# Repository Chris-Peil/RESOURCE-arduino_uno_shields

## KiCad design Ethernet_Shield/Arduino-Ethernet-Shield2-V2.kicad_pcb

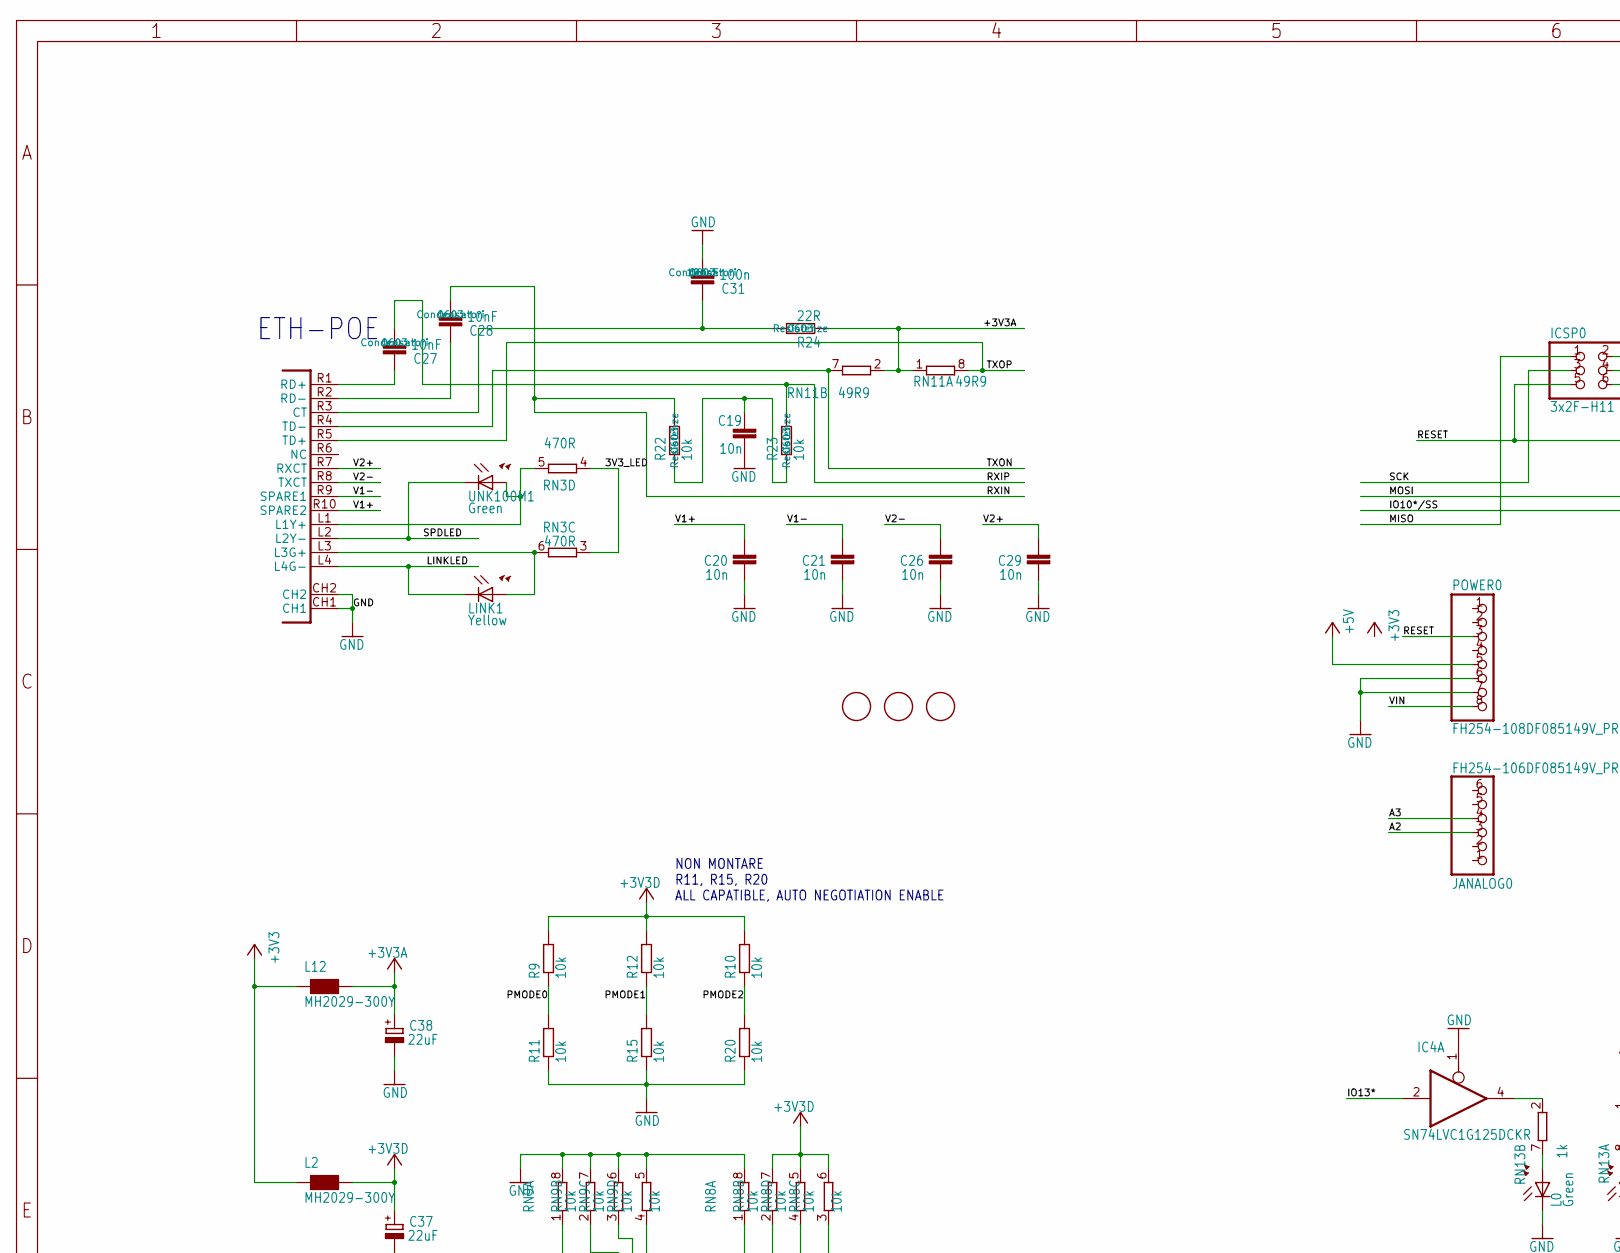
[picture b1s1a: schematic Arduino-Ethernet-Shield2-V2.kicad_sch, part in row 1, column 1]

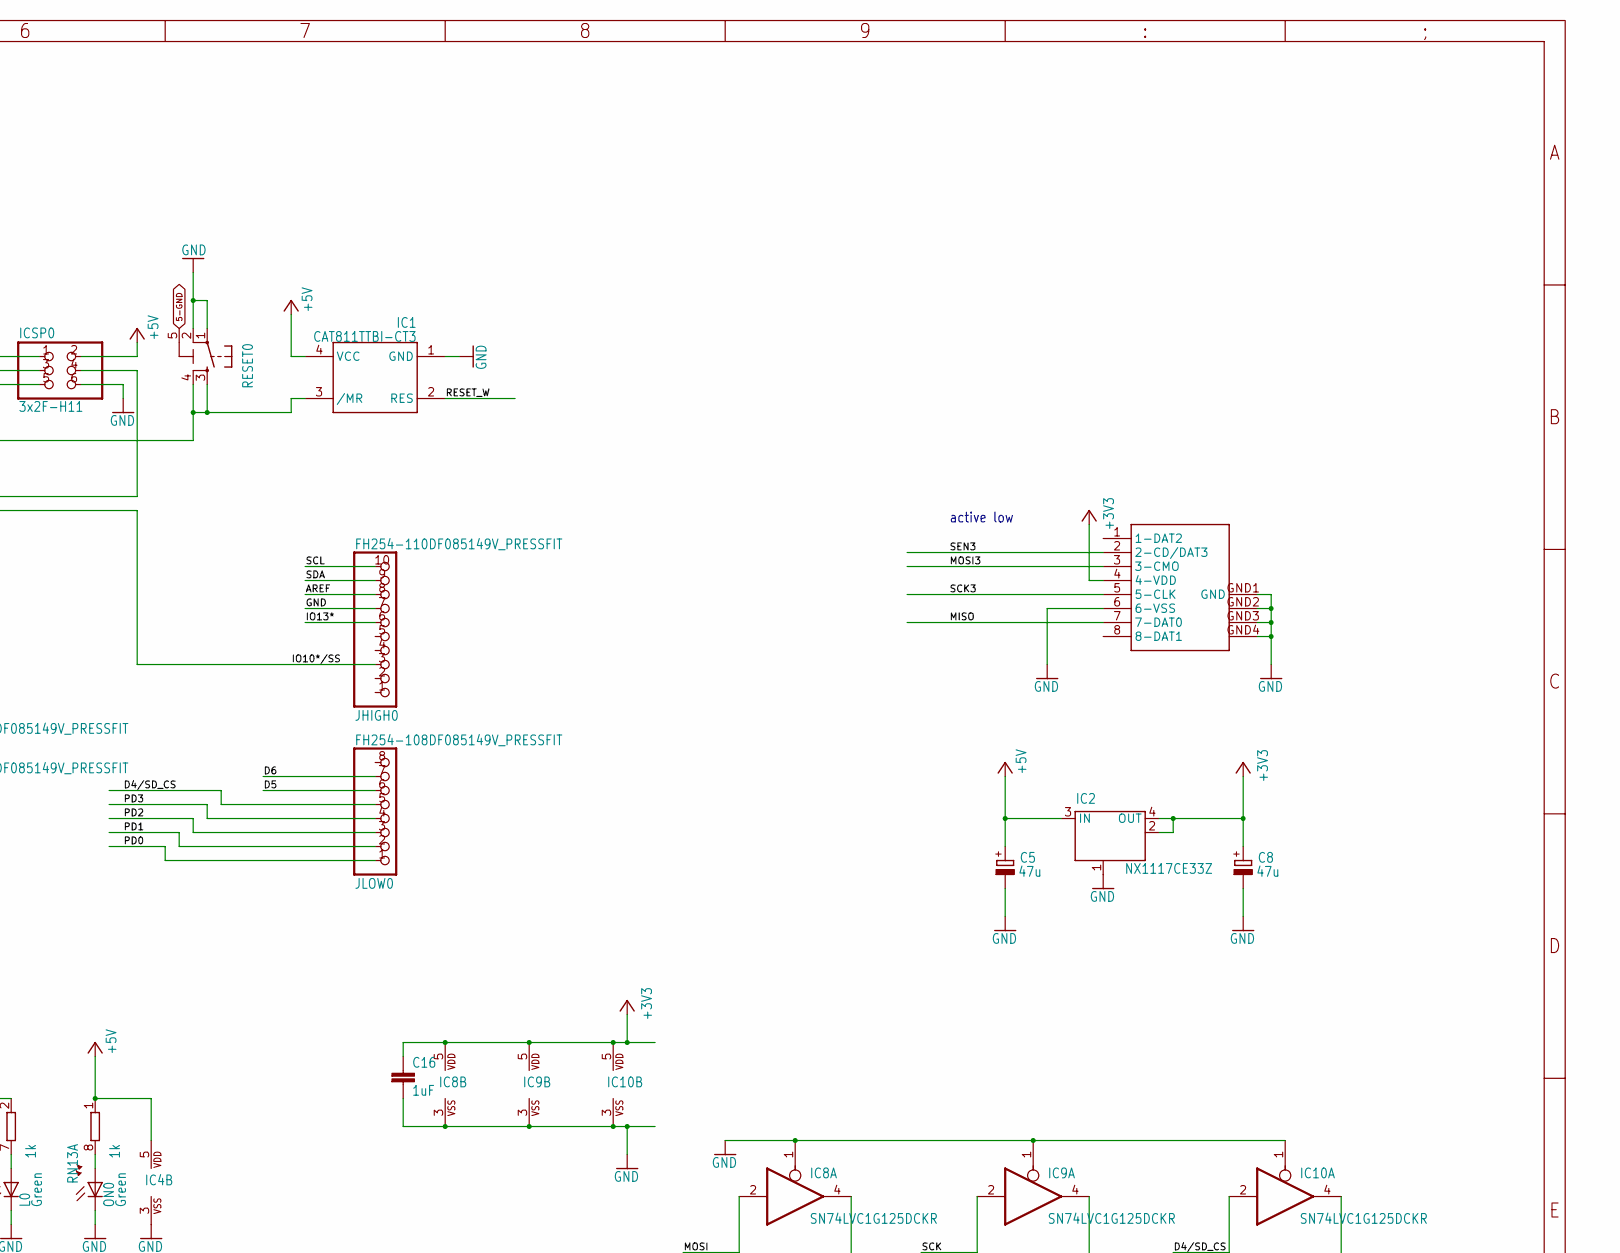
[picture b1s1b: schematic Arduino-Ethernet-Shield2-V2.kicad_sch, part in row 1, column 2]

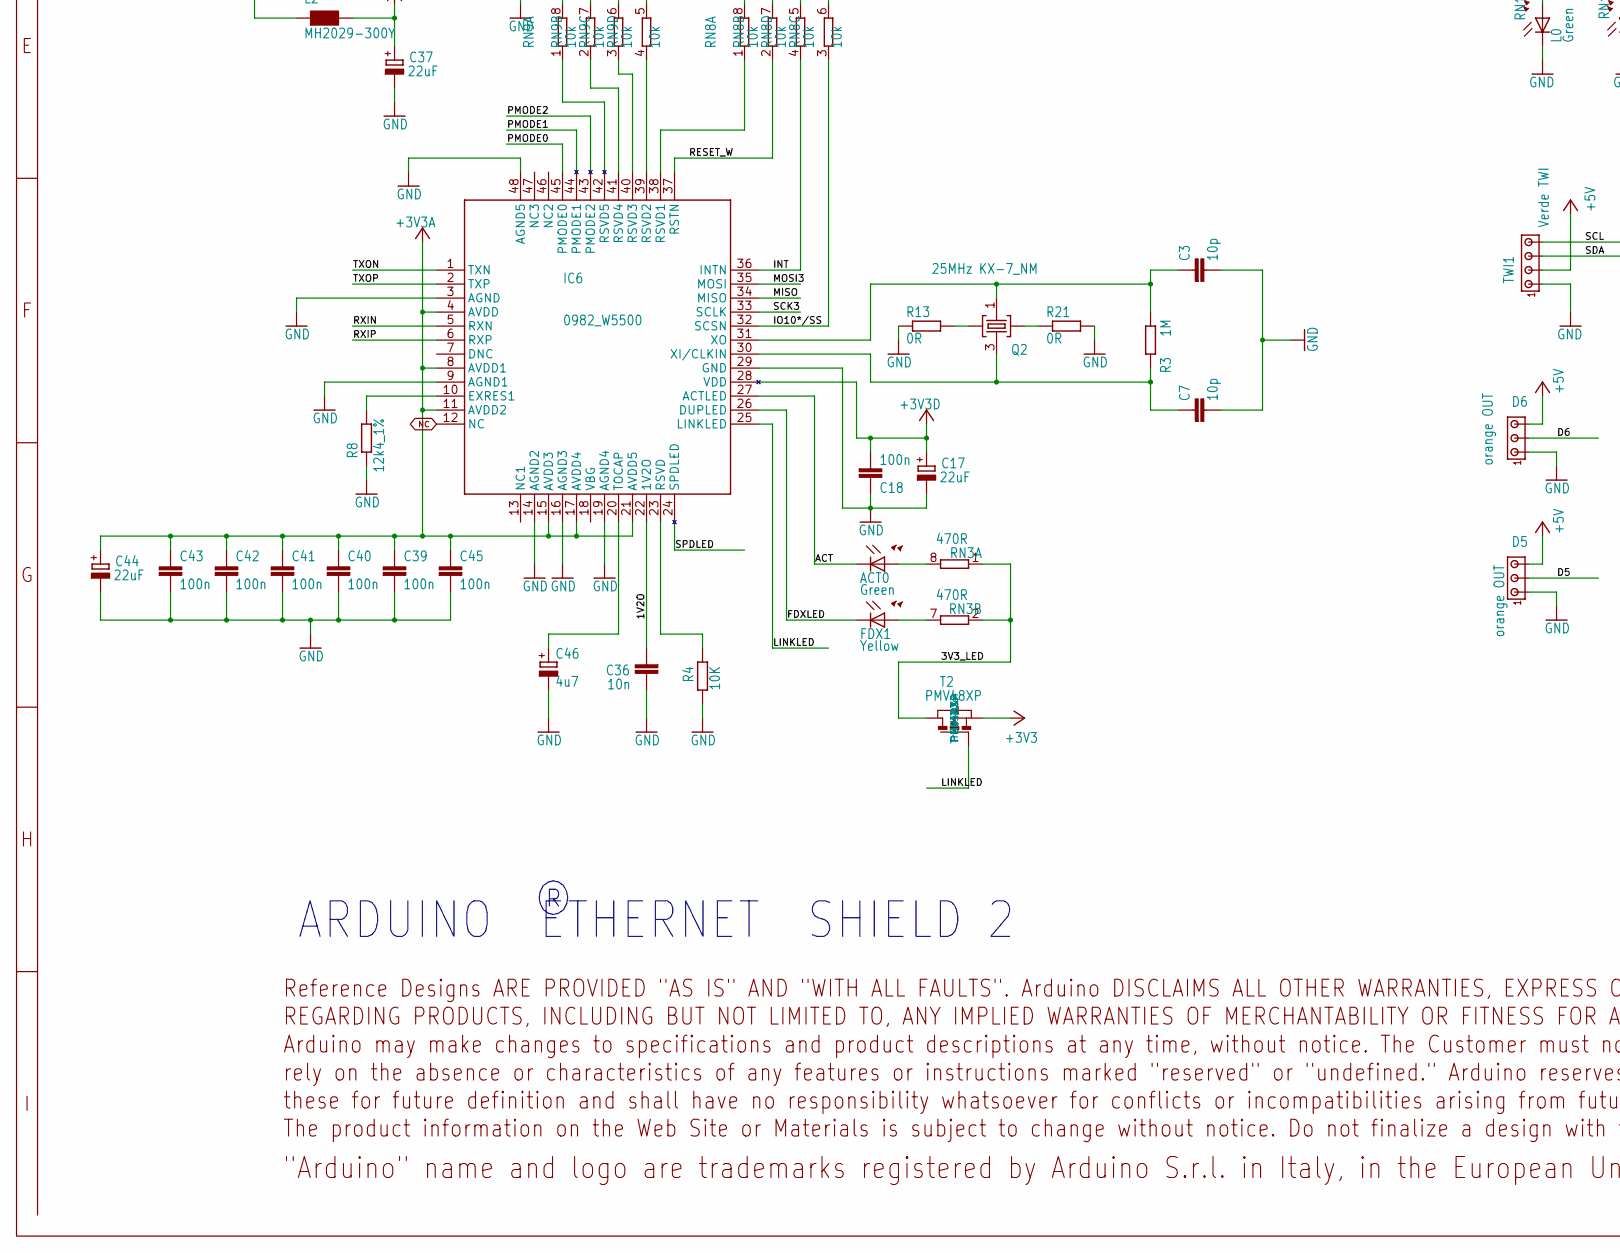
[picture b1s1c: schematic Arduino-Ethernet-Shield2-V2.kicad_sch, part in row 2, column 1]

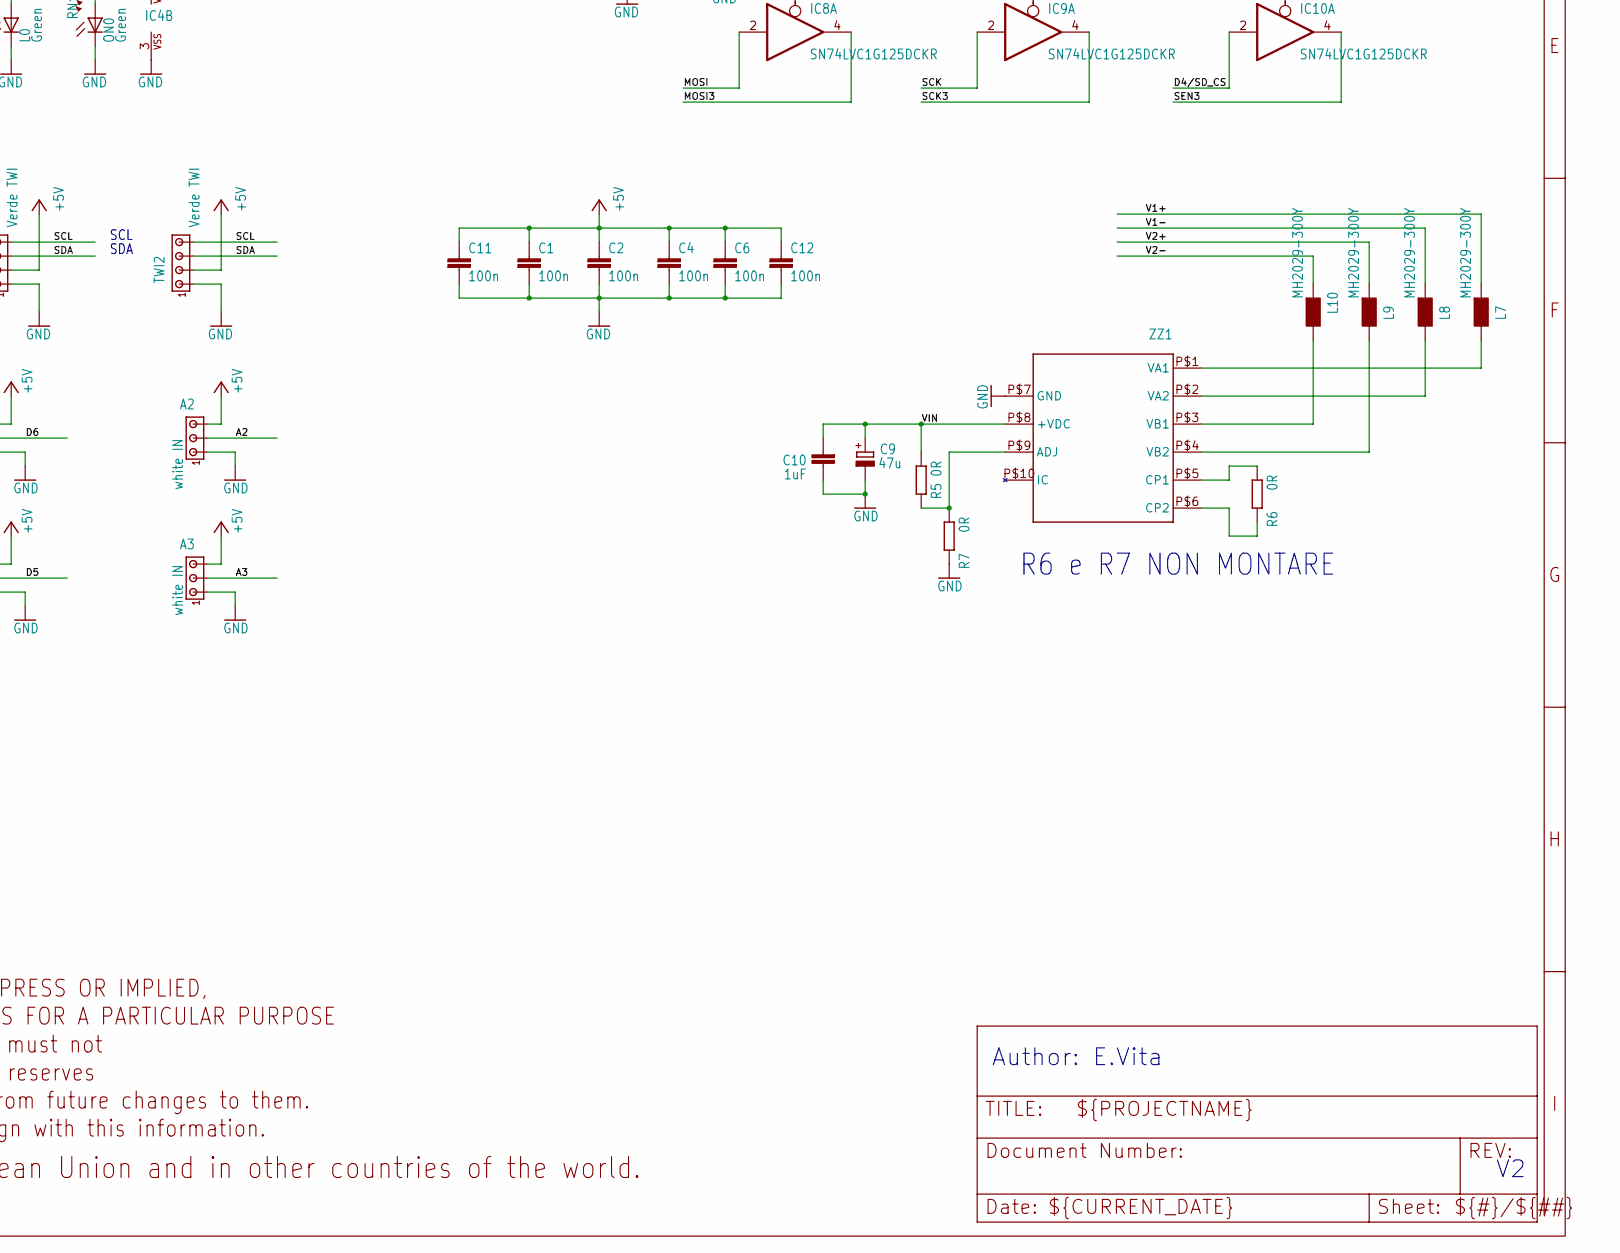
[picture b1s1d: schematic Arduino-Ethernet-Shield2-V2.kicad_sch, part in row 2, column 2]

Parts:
A2, A3: white IN; 10X03MTA
ACT0: Green; CHIPLED_0805
C1, C2, C4, C6, C11, C12, C18, C31, C39, C40, C41, C42, C43, C45: 100n; C0603-ROUND
C3, C7: 10p; C0603-ROUND
C5, C8, C9: 47u; PANASONIC_D
C10, C16: 1uF; C0603-ROUND
C17, C37, C38, C44: 22uF; SMC_B
C19, C20, C21, C26, C29, C36: 10n; C0603-ROUND
C27, C28: 10nF; C0603-ROUND
C46: 4u7; SMC_A
D5, D6: orange OUT; 10X03MTA
FDX1: Yellow; CHIPLED_0805
FID2, FID3, FID4: FIDUCIALMOUNT; FIDUCIA-MOUNT
IC1: CAT811TTBI-CT3; SOT143
IC2: NX1117CE33Z; SOT223
IC4, IC8, IC9, IC10: SN74LVC1G125DCKR; SC70-5
IC6: 0982_W5500; TQFP48-7X7
ICSP0: 3x2F-H11; 2X03
JANALOG0: FH254-106DF085149V_PRESSFIT; 1X06-TH-PRESSFIT
JHIGH0: FH254-110DF085149V_PRESSFIT; 1X10-TH-PRESSFIT
JLOW0: FH254-108DF085149V_PRESSFIT; 1X08-TH-PRESSFIT
L0: Green; CHIPLED_0805
L2, L7, L8, L9, L10, L12: MH2029-300Y; 0805
LINK1: Yellow; CHIPLED_0805
ON0: Green; CHIPLED_0805
POWER0: FH254-108DF085149V_PRESSFIT; 1X08-TH-PRESSFIT
Q2: 25MHz KX-7_NM; CRYSTAL3.2X2.5
R3: 1M; R0603-ROUND
R4: 10K; R0603-ROUND
R5, R6, R7: 0R; R0603-ROUND
R8: 12k4_1%; R0603-ROUND
R9, R10, R11, R12, R15, R20, R22, R23: 10k; R0603-ROUND
R13, R21: 0R; R0402
R24: 22R; R0603-ROUND
RESET0: 0946_TS42031-160W-TR-7260; TS42
RN3: 470R; CAY16
RN8, RN9: 10k; CAY16
RN11: 49R9; CAY16
RN13: 1k; CAY16
T2: PMV48XP; SOT-23; PART_NUMBER PMV48XP
TWI1, TWI2: Verde TWI; 10X04MTA
U$1: DISCLAIMER
UC1: RB1-125BHQ1A; POE-RJ45
UNK100M1: Green; CHIPLED_0805
X1: 0046_15TW-882; SDCARD-15TW-8821
ZZ1: 0343_AG9612-2BR; AG9000

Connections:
1V2O: C36.2, IC6.22 (1V2O)
3V3_LED: RN3.1, RN3.2 (1), RN3.3 (1), RN3.4 (1), T2.1 (D)
5-GND: RESET0.5 (5-GND)
+3V3: C8.+, C16.1, IC2.2 (OUT@1), IC2.4 (OUT), IC8.5 (VDD), IC9.5 (VDD), IC10.5 (VDD), L2.1, L12.1, T2.2 (S), X1.4 (4-VDD)
+3V3A: C38.+, C39.1, C40.1, C41.1, C42.1, C43.1, C44.+, C45.1, IC6.4 (AVDD), IC6.8 (AVDD1), IC6.11 (AVDD2), IC6.15 (AVDD3), IC6.17 (AVDD4), IC6.21 (AVDD5), L12.2, R24.1, RN11.1, RN11.2 (1)
+3V3D: C17.+, C18.2, C37.+, IC6.28 (VDD), L2.2, R9.2, R10.2, R12.2, RN8.5 (2), RN8.6 (2), RN8.7 (2)
+5V: A2.3, A3.3, C1.1, C2.1, C4.1, C5.+, C6.1, C11.1, C12.1, D5.3, D6.3, IC1.4 (VCC), IC2.3 (IN), IC4.5 (VDD), ICSP0.2, POWER0.5, RN13.1, TWI1.2, TWI2.2
A2: A2.2, JANALOG0.3
A3: A3.2, JANALOG0.4
ACT: ACT0.C, IC6.27 (ACTLED)
AREF: JHIGH0.8
D4/SD_CS: IC10.2 (I), JLOW0.5
D5: D5.2, JLOW0.6
D6: D6.2, JLOW0.7
FDXLED: FDX1.C, IC6.26 (DUPLED)
GND: A2.1, A3.1, C1.2, C2.2, C3.2, C4.2, C5.-, C6.2, C7.2, C8.-, C9.-, C10.1, C11.2, C12.2, C16.2, C17.-, C18.1, C19.1, C20.1, C21.1, C26.1, C29.1, C31.1, C36.1, C37.-, C38.-, C39.2, C40.2, C41.2, C42.2, C43.2, C44.-, C45.2, C46.-, D5.1, D6.1, IC1.1 (GND), IC2.1 (GND/ADJ), IC4.1 (OE), IC4.3 (VSS), IC6.3 (AGND), IC6.9 (AGND1), IC6.14 (AGND2), IC6.16 (AGND3), IC6.19 (AGND4), IC6.29 (GND), IC6.48 (AGND5), IC8.1 (OE), IC8.3 (VSS), IC9.1 (OE), IC9.3 (VSS), IC10.1 (OE), IC10.3 (VSS), ICSP0.6, JHIGH0.7, L0.C, ON0.C, POWER0.6, POWER0.7, R4.1, R7.2, R8.1, R11.1, R13.1, R15.1, R20.1, R21.2, RESET0.1, RESET0.2, RN8.8 (2), RN9.5 (2), RN9.6 (2), RN9.7 (2), RN9.8 (2), TWI1.1, TWI2.1, UC1.CH1, UC1.CH2, X1.6 (6-VSS), X1.GND1 (GND), X1.GND2 (GND1), X1.GND3 (GND2), X1.GND4 (GND3), ZZ1.P$7 (GND)
INT: IC6.36 (INTN), RN8.4 (1)
IO10*/SS: IC6.32 (SCSN), JHIGH0.3, RN8.3 (1)
IO13*: IC4.2 (I), JHIGH0.6
LINKLED: IC6.25 (LINKLED), LINK1.C, T2.3 (G), UC1.L4 (L4G-)
MISO: IC6.34 (MISO), ICSP0.1, X1.7 (7-DAT0)
MOSI: IC8.2 (I), ICSP0.4
MOSI3: IC6.35 (MOSI), IC8.4 (O), X1.3 (3-CMO)
unnamed: L7.2, ZZ1.P$1 (VA1)
unnamed: L8.2, ZZ1.P$2 (VA2)
unnamed: L9.2, ZZ1.P$4 (VB2)
unnamed: L10.2, ZZ1.P$3 (VB1)
unnamed: C3.1, IC6.31 (XO), Q2.1, R3.1
unnamed: IC6.39 (RSVD2), RN9.4 (1)
unnamed: ACT0.A, RN3.8 (2)
unnamed: Q2.2, R13.2
unnamed: Q2.4, R21.1
unnamed: LINK1.A, RN3.6 (2), UC1.L3 (L3G+)
unnamed: IC6.23 (RSVD), R4.2
unnamed: RN3.5 (2), UC1.L1 (L1Y+), UNK100M1.A
unnamed: C19.2, R22.1, R23.1
unnamed: C27.2, UC1.R1 (RD+)
unnamed: C28.2, UC1.R2 (RD-)
unnamed: FDX1.A, RN3.7 (2)
unnamed: IC6.40 (RSVD3), RN9.3 (1)
unnamed: R6.1, ZZ1.P$5 (CP1)
unnamed: R6.2, ZZ1.P$6 (CP2)
unnamed: R5.2, R7.1, ZZ1.P$9 (ADJ)
unnamed: IC6.41 (RSVD4), RN9.2 (1)
unnamed: C31.2, R24.2, UC1.R3 (CT)
unnamed: IC6.42 (RSVD5), RN9.1
unnamed: C46.+, IC6.20 (TOCAP)
unnamed: IC6.38 (RSVD1), RN8.1
unnamed: IC6.10 (EXRES1), R8.2
unnamed: ON0.A, RN13.8 (2)
unnamed: IC4.4 (O), RN13.2 (1)
unnamed: L0.A, RN13.7 (2)
NC: IC6.12 (NC)
OSC2E2: C7.1, IC6.30 (XI/CLKIN), Q2.3, R3.2
PD0: JLOW0.1
PD1: JLOW0.2
PD2: JLOW0.3
PD3: JLOW0.4
PMODE0: IC6.45 (PMODE0), R9.1, R11.2
PMODE1: IC6.44 (PMODE1), R12.1, R15.2
PMODE2: IC6.43 (PMODE2), R10.1, R20.2
RESET: IC1.3 (/MR), ICSP0.5, POWER0.3, RESET0.3, RESET0.4
RESET_W: IC1.2 (RES), IC6.37 (RSTN), RN8.2 (1)
RXIN: C28.1, IC6.5 (RXN), R22.2
RXIP: C27.1, IC6.6 (RXP), R23.2
SCK: IC9.2 (I), ICSP0.3
SCK3: IC6.33 (SCLK), IC9.4 (O), X1.5 (5-CLK)
SCL: JHIGH0.10, TWI1.4, TWI2.4
SDA: JHIGH0.9, TWI1.3, TWI2.3
SEN3: IC10.4 (O), X1.2 (2-CD/DAT3)
SPDLED: IC6.24 (SPDLED), UC1.L2 (L2Y-), UNK100M1.C
TXON: IC6.1 (TXN), RN11.7 (2), UC1.R4 (TD-)
TXOP: IC6.2 (TXP), RN11.8 (2), UC1.R5 (TD+)
V1+: C20.2, L7.1, UC1.R10 (SPARE2)
V1-: C21.2, L8.1, UC1.R9 (SPARE1)
V2+: C29.2, L9.1, UC1.R7 (RXCT)
V2-: C26.2, L10.1, UC1.R8 (TXCT)
VIN: C9.+, C10.2, POWER0.8, R5.1, ZZ1.P$8 (+VDC)

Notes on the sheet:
ARDUINO ETHERNET SHIELD 2
SDA
ETH-POE
Author: E.Vita
R6 e R7 NON MONTARE
NON MONTARE R11, R15, R20 ALL CAPATIBLE, AUTO NEGOTIATION ENABLE
active low
SCL

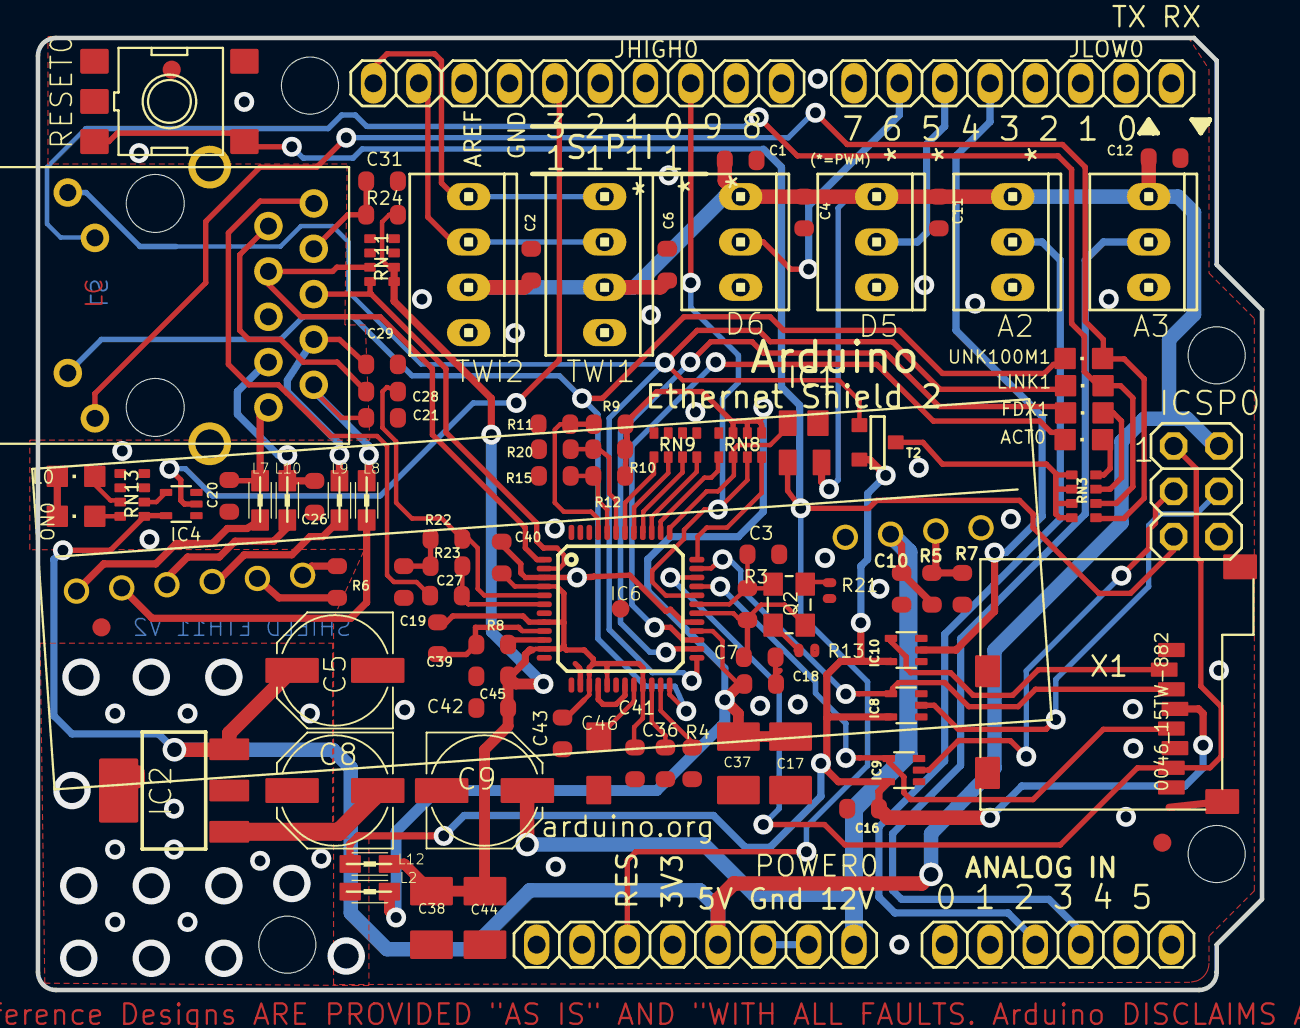
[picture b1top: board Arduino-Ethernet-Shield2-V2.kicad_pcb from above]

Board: 2 copper layers, 68.6 x 53.3 mm, 100 parts (0 on the bottom side), 71 nets.

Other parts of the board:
UNK_HOLE_0: dummyfp0
UNK_HOLE_1: dummyfp1
UNK_HOLE_2: dummyfp2
UNK_HOLE_3: dummyfp3

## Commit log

2025-12-07 +synth shield, +ethernet shield
2025-12-07 started template shield schematic
2025-12-07 added connector footprints
2025-12-08 added datasheet and header models to PCB
